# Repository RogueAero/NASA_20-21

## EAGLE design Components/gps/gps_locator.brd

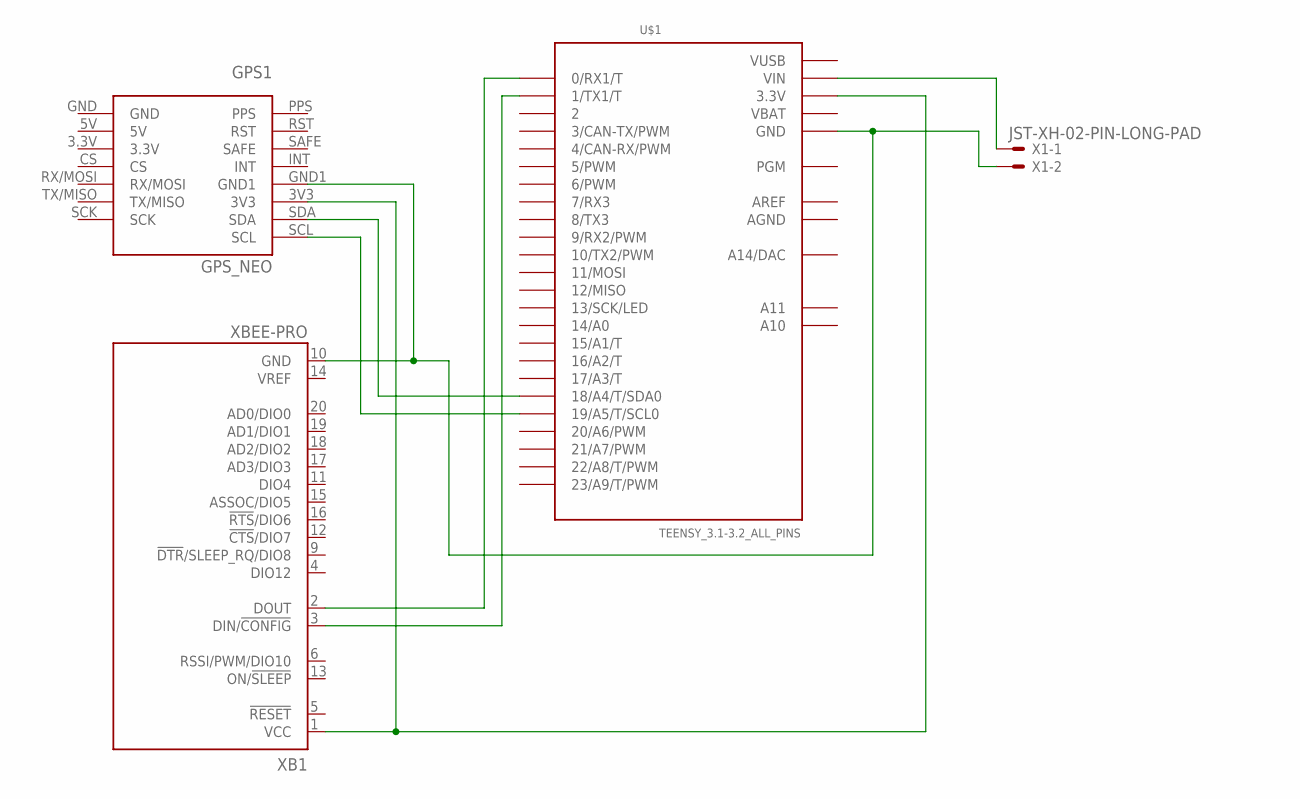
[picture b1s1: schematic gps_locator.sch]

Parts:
GPS1: GPS_NEO
U$1: TEENSY_3.1-3.2_ALL_PINS; TEENSY_3.0-3.2&LC_ALL_PINS
X1: JST-XH-02-PIN-LONG-PAD; JST-XH-02-PACKAGE-LONG-PAD
XB1: XBEE-PRO

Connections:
AGND: U$1.AGND
AREF: U$1.AREF
unnamed: U$1.VIN, X1.1
unnamed: GPS1.GND1, U$1.GND, U$1.GND1 (GND), X1.2, XB1.10 (GND)
unnamed: U$1.1 (1/TX1/T), XB1.3 (DIN/!CONFIG)
unnamed: GPS1.3V3, U$1.3.3V, U$1.3.3V1 (3.3V), XB1.1 (VCC)
unnamed: U$1.0 (0/RX1/T), XB1.2 (DOUT)
unnamed: GPS1.SDA, U$1.18/A4 (18/A4/T/SDA0)
unnamed: GPS1.SCL, U$1.19/A5 (19/A5/T/SCL0)
VBAT: U$1.VBAT
VUSB: U$1.VUSB

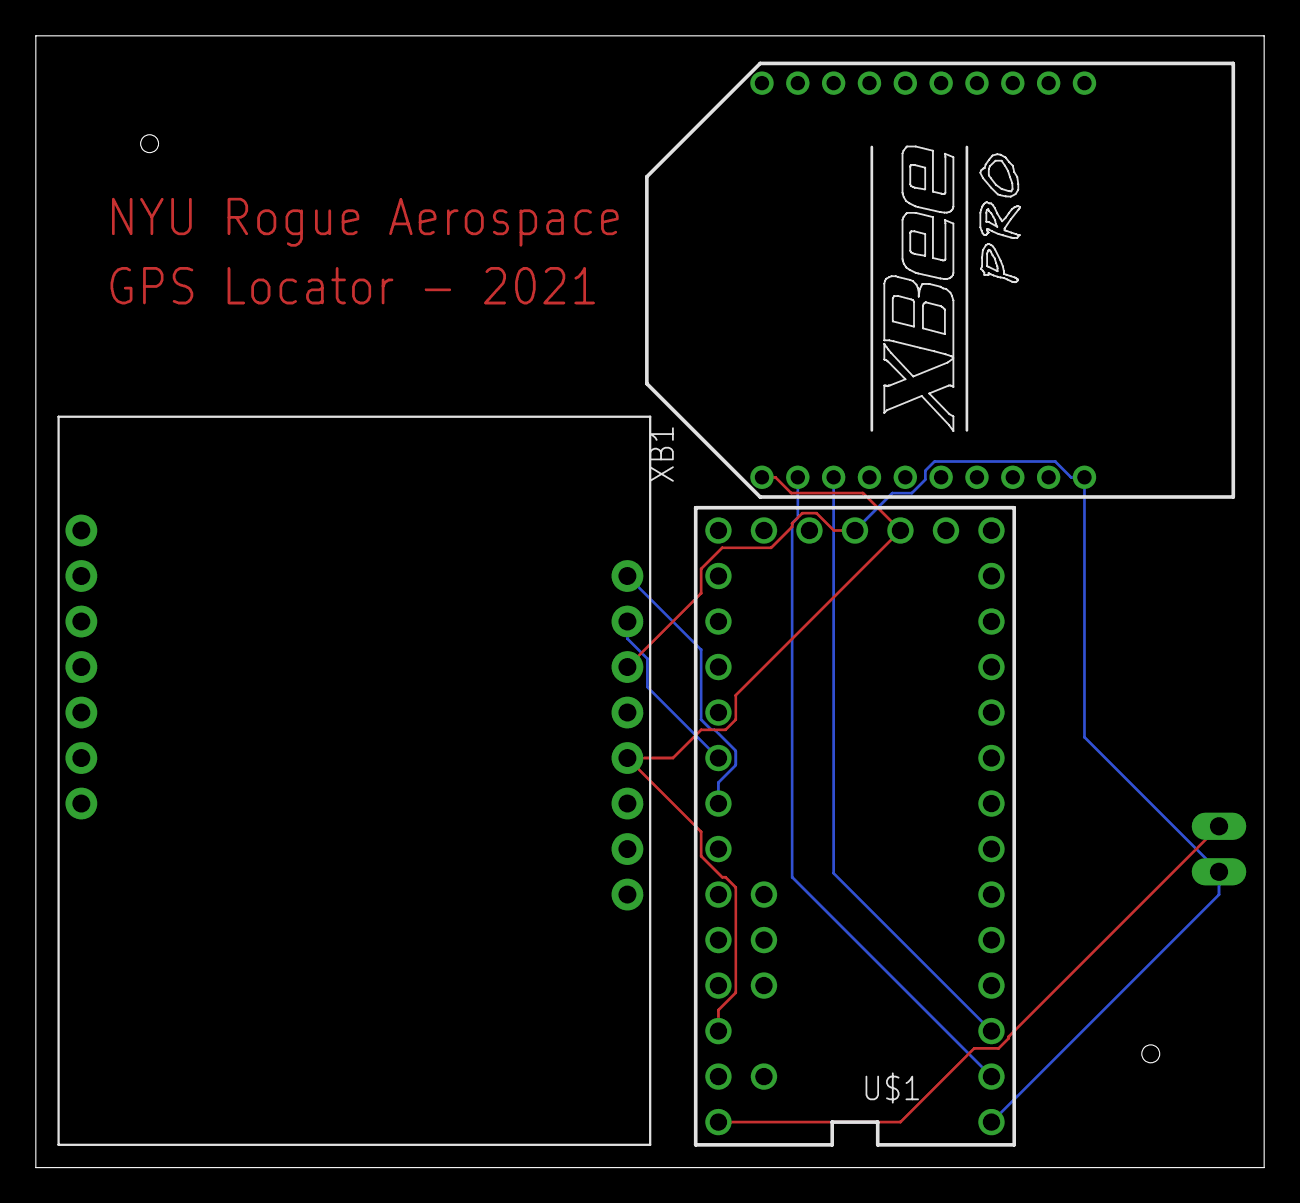
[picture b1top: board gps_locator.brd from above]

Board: 2 copper layers, 68.6 x 63.2 mm, 4 parts (1 on the bottom side), 7 nets.

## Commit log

2020-10-14 Create camera
2020-10-14 adding base folders for component code
2020-10-14 added pseudofiles
2020-10-14 Create code.c
    Added code for actuators.
2020-10-20 Create camera stuff
2020-10-21 added example code for python image stitching
2020-10-21 Add arduino file
2020-10-28 Add files via upload
    GPS Module Test Code
2020-11-11 Test code for xbee transmitter and receivers
2020-11-11 Coordinator module and remote module example code
2020-11-25 Actuator code complete v1
2020-12-09 testing image display code
2020-12-09 image to play around with
2020-12-28 new file
2021-04-16 gps board and schematic
2021-04-30 Satellite image of the launch site
    bottom left: (41.315917, -74.490298)
    top left: (41.315917, -74.488976)
    top right: (41.334287, -74.488976)
    bottom right: (41.334287, -74.488976)
2021-04-30 ground station stuff
2021-05-02 removed filler file
2021-05-02 removed test picture
2021-05-02 added drawing capabilities, added timer event for updating
2021-05-03 implemented moving Locator
2021-05-03 removed filler text files
